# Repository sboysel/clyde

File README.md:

# clyde

- split ortholinear
- MX 36 keys (layout inspired by [weteor/Kong](https://github.com/weteor/Kong))
- RJ45 split comms
- WeAct RP2040 Pi Pico
- PCB: diodeless, reversible, hotswap

See `BOM` for complete list of parts and relevant numbers. Gerbers for PCB and switch plate in `prod`. Outline for bottom plate in `ergogen/outlines`.

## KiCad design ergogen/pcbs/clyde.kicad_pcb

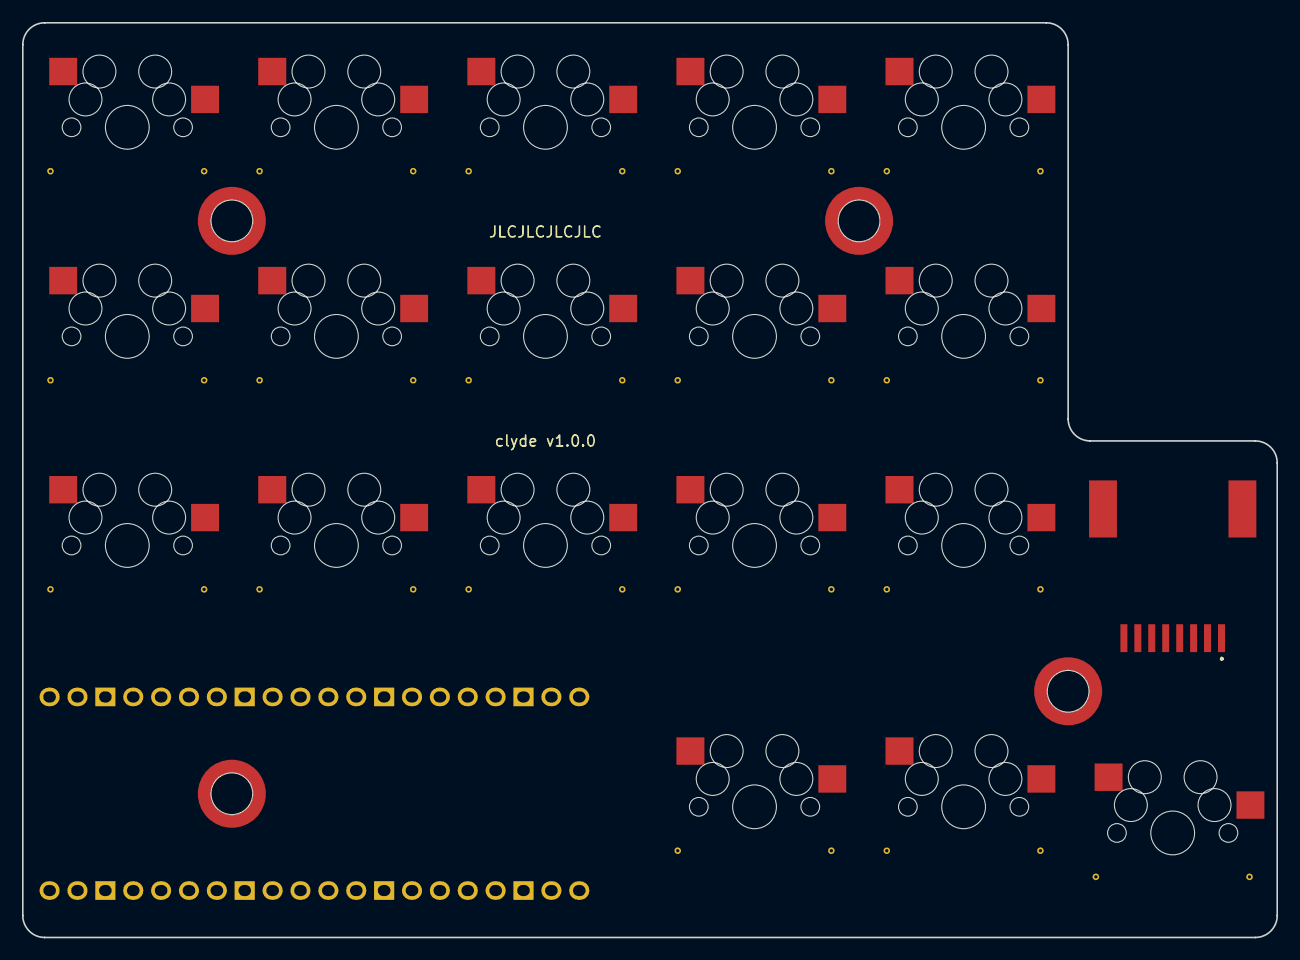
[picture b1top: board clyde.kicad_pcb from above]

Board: 2 copper layers, 114.3 x 83.3 mm, 19 parts (0 on the bottom side), 19 nets, no tracks yet.

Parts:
S1, S2, S3, S4, S5, S6, S7, S8, S9, S10, S11, S12, S13, S14, S15, S16, S17, S18: MX
U0: RPi_Pico_TH_oval_face_down

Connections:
GND: S1.2, S2.2, S3.2, S4.2, S5.2, S6.2, S7.2, S8.2, S9.2, S10.2, S11.2, S12.2, S13.2, S14.2, S15.2, S16.2, S17.2, S18.2, U0.3, U0.8, U0.13, U0.18, U0.23, U0.28, U0.33, U0.38
matrix_index_bottom: S10.1, U0.15
matrix_index_home: S11.1, U0.14
matrix_index_top: S12.1, U0.12
matrix_inner_bottom: S13.1, U0.16
matrix_inner_home: S14.1, U0.17
matrix_inner_top: S15.1, U0.19
matrix_middle_bottom: S7.1, U0.11
matrix_middle_home: S8.1, U0.10
matrix_middle_top: S9.1, U0.9
matrix_pinky_bottom: S1.1, U0.4
matrix_pinky_home: S2.1, U0.2
matrix_pinky_top: S3.1, U0.1
matrix_ring_bottom: S4.1, U0.5
matrix_ring_home: S5.1, U0.6
matrix_ring_top: S6.1, U0.7
thumb_far_mods: S18.1, U0.24
thumb_middle_mods: S17.1, U0.25
thumb_near_mods: S16.1, U0.26

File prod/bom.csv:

Designator,Footprint,Quantity,Value,LCSC Part #
"S1, S10, S11, S12, S13, S14, S15, S16, S17, S18, S2, S3, S4, S5, S6, S7, S8, S9",MX,18,,
TRRS1,TRRS-PJ-320A-dual,1,TRRS-PJ-320A-dual,
U0,RPi_Pico_TH_oval_face_down,1,,
"_4, _5, _6, _7",MountingHole_2.2mm_M2_Pad_Via,4,,

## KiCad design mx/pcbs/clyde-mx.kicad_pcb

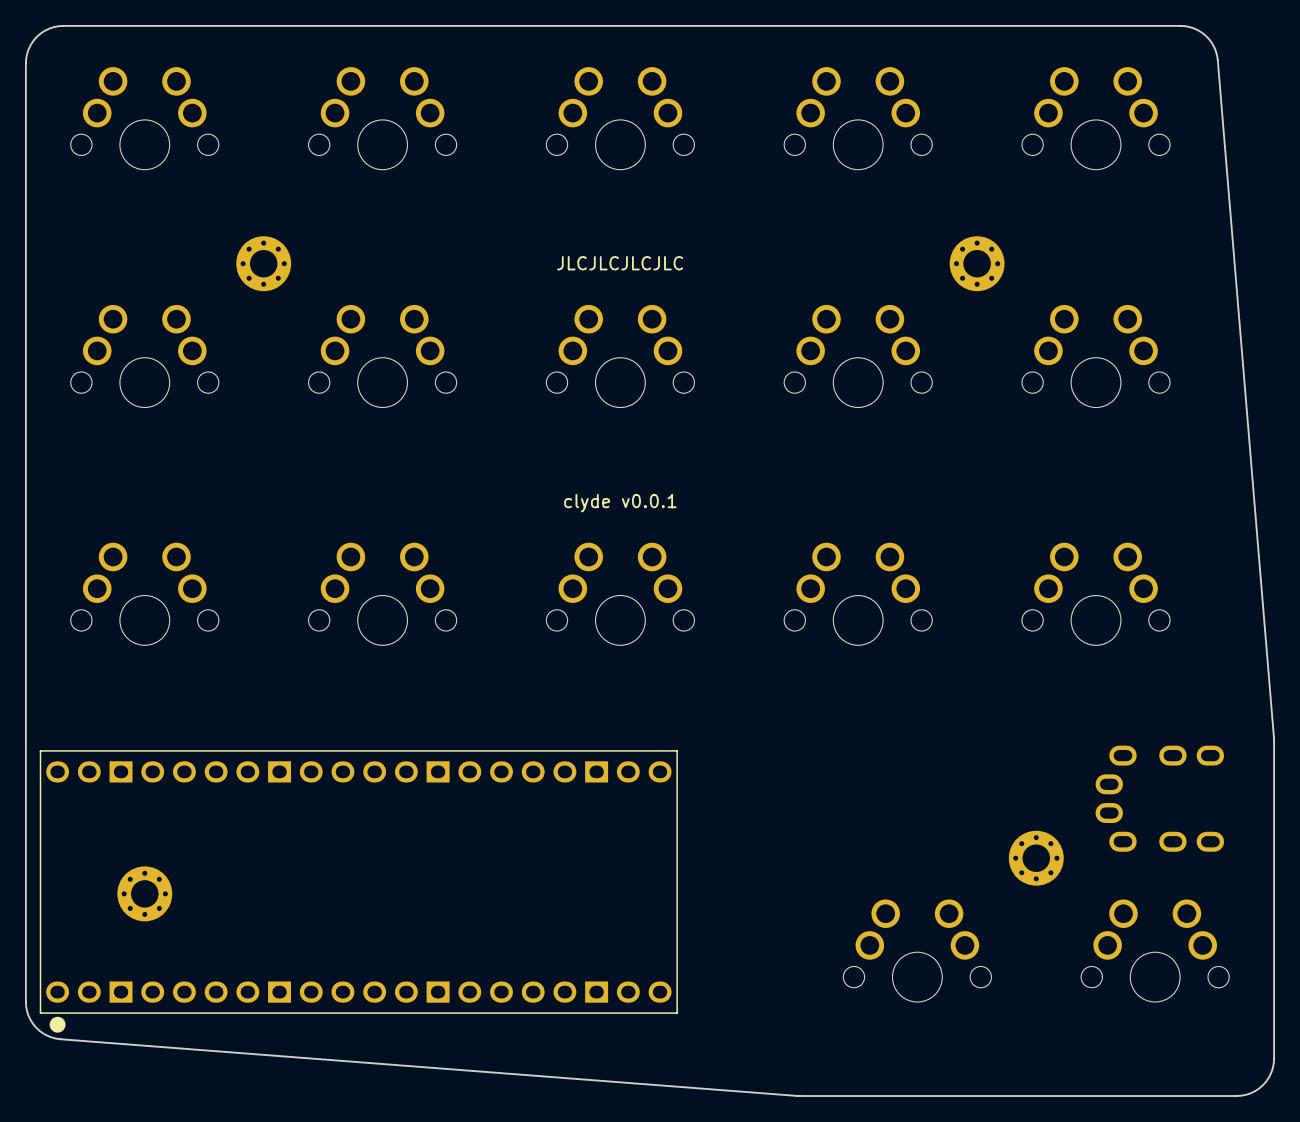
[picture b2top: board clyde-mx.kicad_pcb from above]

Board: 2 copper layers, 100.0 x 85.7 mm, 23 parts (0 on the bottom side), 21 nets, no tracks yet.

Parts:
S1, S2, S3, S4, S5, S6, S7, S8, S9, S10, S11, S12, S13, S14, S15, S16, S17: MX
TRRS1: TRRS-PJ-320A-dual
U0: Pico; RPi_Pico_TH_oval_face_up
_4, _5, _6, _7: MountingHole_2.2mm_M2_Pad_Via

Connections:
GND: S1.2, S2.2, S3.2, S4.2, S5.2, S6.2, S7.2, S8.2, S9.2, S10.2, S11.2, S12.2, S13.2, S14.2, S15.2, S16.2, S17.2, TRRS1.2, U0.3, U0.8, U0.13, U0.18, U0.23, U0.28, U0.33, U0.38
GP8: TRRS1.3, TRRS1.4, U0.11
GP9: TRRS1.3, TRRS1.4, U0.12
VSYS: TRRS1.1, U0.39
matrix_index_bottom: S10.1, U0.21
matrix_index_home: S11.1, U0.22
matrix_index_top: S12.1, U0.24
matrix_inner_bottom: S13.1, U0.20
matrix_inner_home: S14.1, U0.19
matrix_inner_top: S15.1, U0.17
matrix_middle_bottom: S7.1, U0.25
matrix_middle_home: S8.1, U0.26
matrix_middle_top: S9.1, U0.27
matrix_pinky_bottom: S1.1, U0.32
matrix_pinky_home: S2.1, U0.34
matrix_pinky_top: S3.1, U0.36
matrix_ring_bottom: S4.1, U0.31
matrix_ring_home: S5.1, U0.30
matrix_ring_top: S6.1, U0.29
thumbfan_far_home: S17.1, U0.15
thumbfan_near_home: S16.1, U0.16

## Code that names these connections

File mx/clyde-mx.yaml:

units:
  kx: U
  ky: U
  px: 100 - 5kx - 0.01
  mh_diam: 2.2    # mounting hole diameter
  mh_pad: 2   # mounting hole copper pad width

points:
  zones:
    matrix:
      anchor:
        shift: [8kx, -8ky]
      columns:
        pinky:
        ring:
        middle:
        index:
        inner:
      rows:
        bottom:
        home:
        top:
    thumbfan:
      anchor:
        ref: matrix_index_bottom
        shift: [px, -1.5ky]
      columns:
        near:
        far:
      rows:
        home:
  key:
    padding: 1ky
    spread: 1kx

outlines:
  _switches:
    - what: rectangle
      where: true
      size: 14
      bound: false
  clyde-mx-bottom-plate:
    - what: polygon
      points:
        # NW
        - ref: matrix_pinky_top
          shift: [-0.5kx, 0.5ky]
        # NE
        - ref: matrix_inner_top
          shift: [0.5kx, 0.5ky]
        # SE
        - ref: matrix_inner_bottom
          shift: [px + 0.5kx, -0.5ky]
        - ref: thumbfan_far_home
          shift: [0.5kx, -0.5ky]
        - ref: thumbfan_near_home
          shift: [-0.5kx, -0.5ky]
        # SW
        - ref: matrix_pinky_bottom
          shift: [-0.5kx, -0.5ky - 1.25ky]
      fillet: 3

pcbs:
  clyde-mx:
    outlines:
      main:
        outline: clyde-mx-bottom-plate
        footprints:
    footprints:
      mx:
        what: mx
        where: true
        params:
          keycaps: true
          reverse: true
          hotswap: false
          from: "{{name}}"
          to: GND 
      pico:
        what: weact_pi_pico
        where:
          ref: matrix_ring_bottom
          shift: [-0.1kx, -1.1ky]
          rotate: 90
        params:
          GP24: matrix_pinky_top
          GP29: matrix_pinky_home
          GP28: matrix_pinky_bottom
          GP27: matrix_ring_bottom
          GP26: matrix_ring_home
          GP22: matrix_ring_top
          GP21: matrix_middle_top
          GP20: matrix_middle_home
          GP19: matrix_middle_bottom
          GP18: matrix_index_top
          GP17: matrix_index_home
          GP16: matrix_index_bottom
          GP15: matrix_inner_bottom
          GP14: matrix_inner_home
          GP13: matrix_inner_top
          GP12: thumbfan_near_home
          GP11: thumbfan_far_home
      trrs:
        what: trrs
        where:
          ref: thumbfan_far_home
          shift: [0.4kx, 0.69ky]
          rotate: 270
        params:
          A: VSYS  # ring
          B: GND   # ring
          C: GP8   # TX
          D: GP9   # RX
          reverse: true
          symmetric: false
          cross: true
          stabilizers: false
      jlc_text:
        what: text 
        where:
          ref: matrix_middle_top
          shift: [0, -0.5ky]
        params:
          text: 'JLCJLCJLCJLC'
      version_text:
        what: text 
        where:
          ref: matrix_middle_home
          shift: [0, -0.5ky]
        params:
          text: 'clyde v0.0.1'
      mh_thumbfan:
        what: mountinghole 
        where:
          ref: thumbfan_near_home
          shift: [0.5kx, 0.5ky]
      mh_mcu:
        what: mountinghole 
        where:
          ref: matrix_pinky_bottom
          shift: [0, -1.15ky]
      mh_pinky:
        what: mountinghole 
        where:
          ref: matrix_pinky_home
          shift: [0.5kx, 0.5ky]
      mh_index:
        what: mountinghole 
        where:
          ref: matrix_index_home
          shift: [0.5kx, 0.5ky]

      # m2_ne:
      #   what: m2 
      #   where:
      #     ref: matrix_inner_home
      #     shift: [-0.5kx, 0.5ky]
      #   params:
      #     drill: mh_diam 
      #     pad: mh_diam + mh_pad
      # m2_se:
      #   what: m2 
      #   where:
      #     ref: matrix_inner_mod
      #     shift: [-0.5kx, 0.5ky]
      #   params:
      #     drill: mh_diam 
      #     pad: mh_diam + mh_pad
      # m2_sw:
      #   what: m2 
      #   where:
      #     ref: matrix_outer_mod
      #     shift: [0.5kx, 0.5ky]
      #   params:
      #     drill: mh_diam 
      #     pad: mh_diam + mh_pad

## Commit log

2023-07-27 36 key version
2023-07-27 hatch groundfill; star silkscreen
2023-07-30 stagger thumb cluster
2023-07-30 prototypes ordered
2023-08-04 layout like split weteor/Kong; outline tweaks
2023-08-04 fix some routing irregularities
2023-09-19 begin work on v1
2023-09-19 working on plate case
2023-10-28 rj45, PCB solder nuts, acrylic bottom plate
2023-10-28 finish routing
2023-10-28 set to JLC
2024-02-02 v1 (#1)
    * 36 key version
    * layout like split weteor/Kong; outline tweaks
    * rj45, PCB solder nuts, acrylic bottom plate
    * JLCPCB prototypes received and operational
2024-02-02 update images
2024-02-03 add BOM
2024-02-05 add firmware

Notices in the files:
README.md:
License: CC BY-SA 4.0
